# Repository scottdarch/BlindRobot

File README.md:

```
.            ``
      <X X>  /
 ``---  |  -
     [     ]   A BlindRobot Project (by 32bits.io)
 _____U___U____________________________________________________________________
```

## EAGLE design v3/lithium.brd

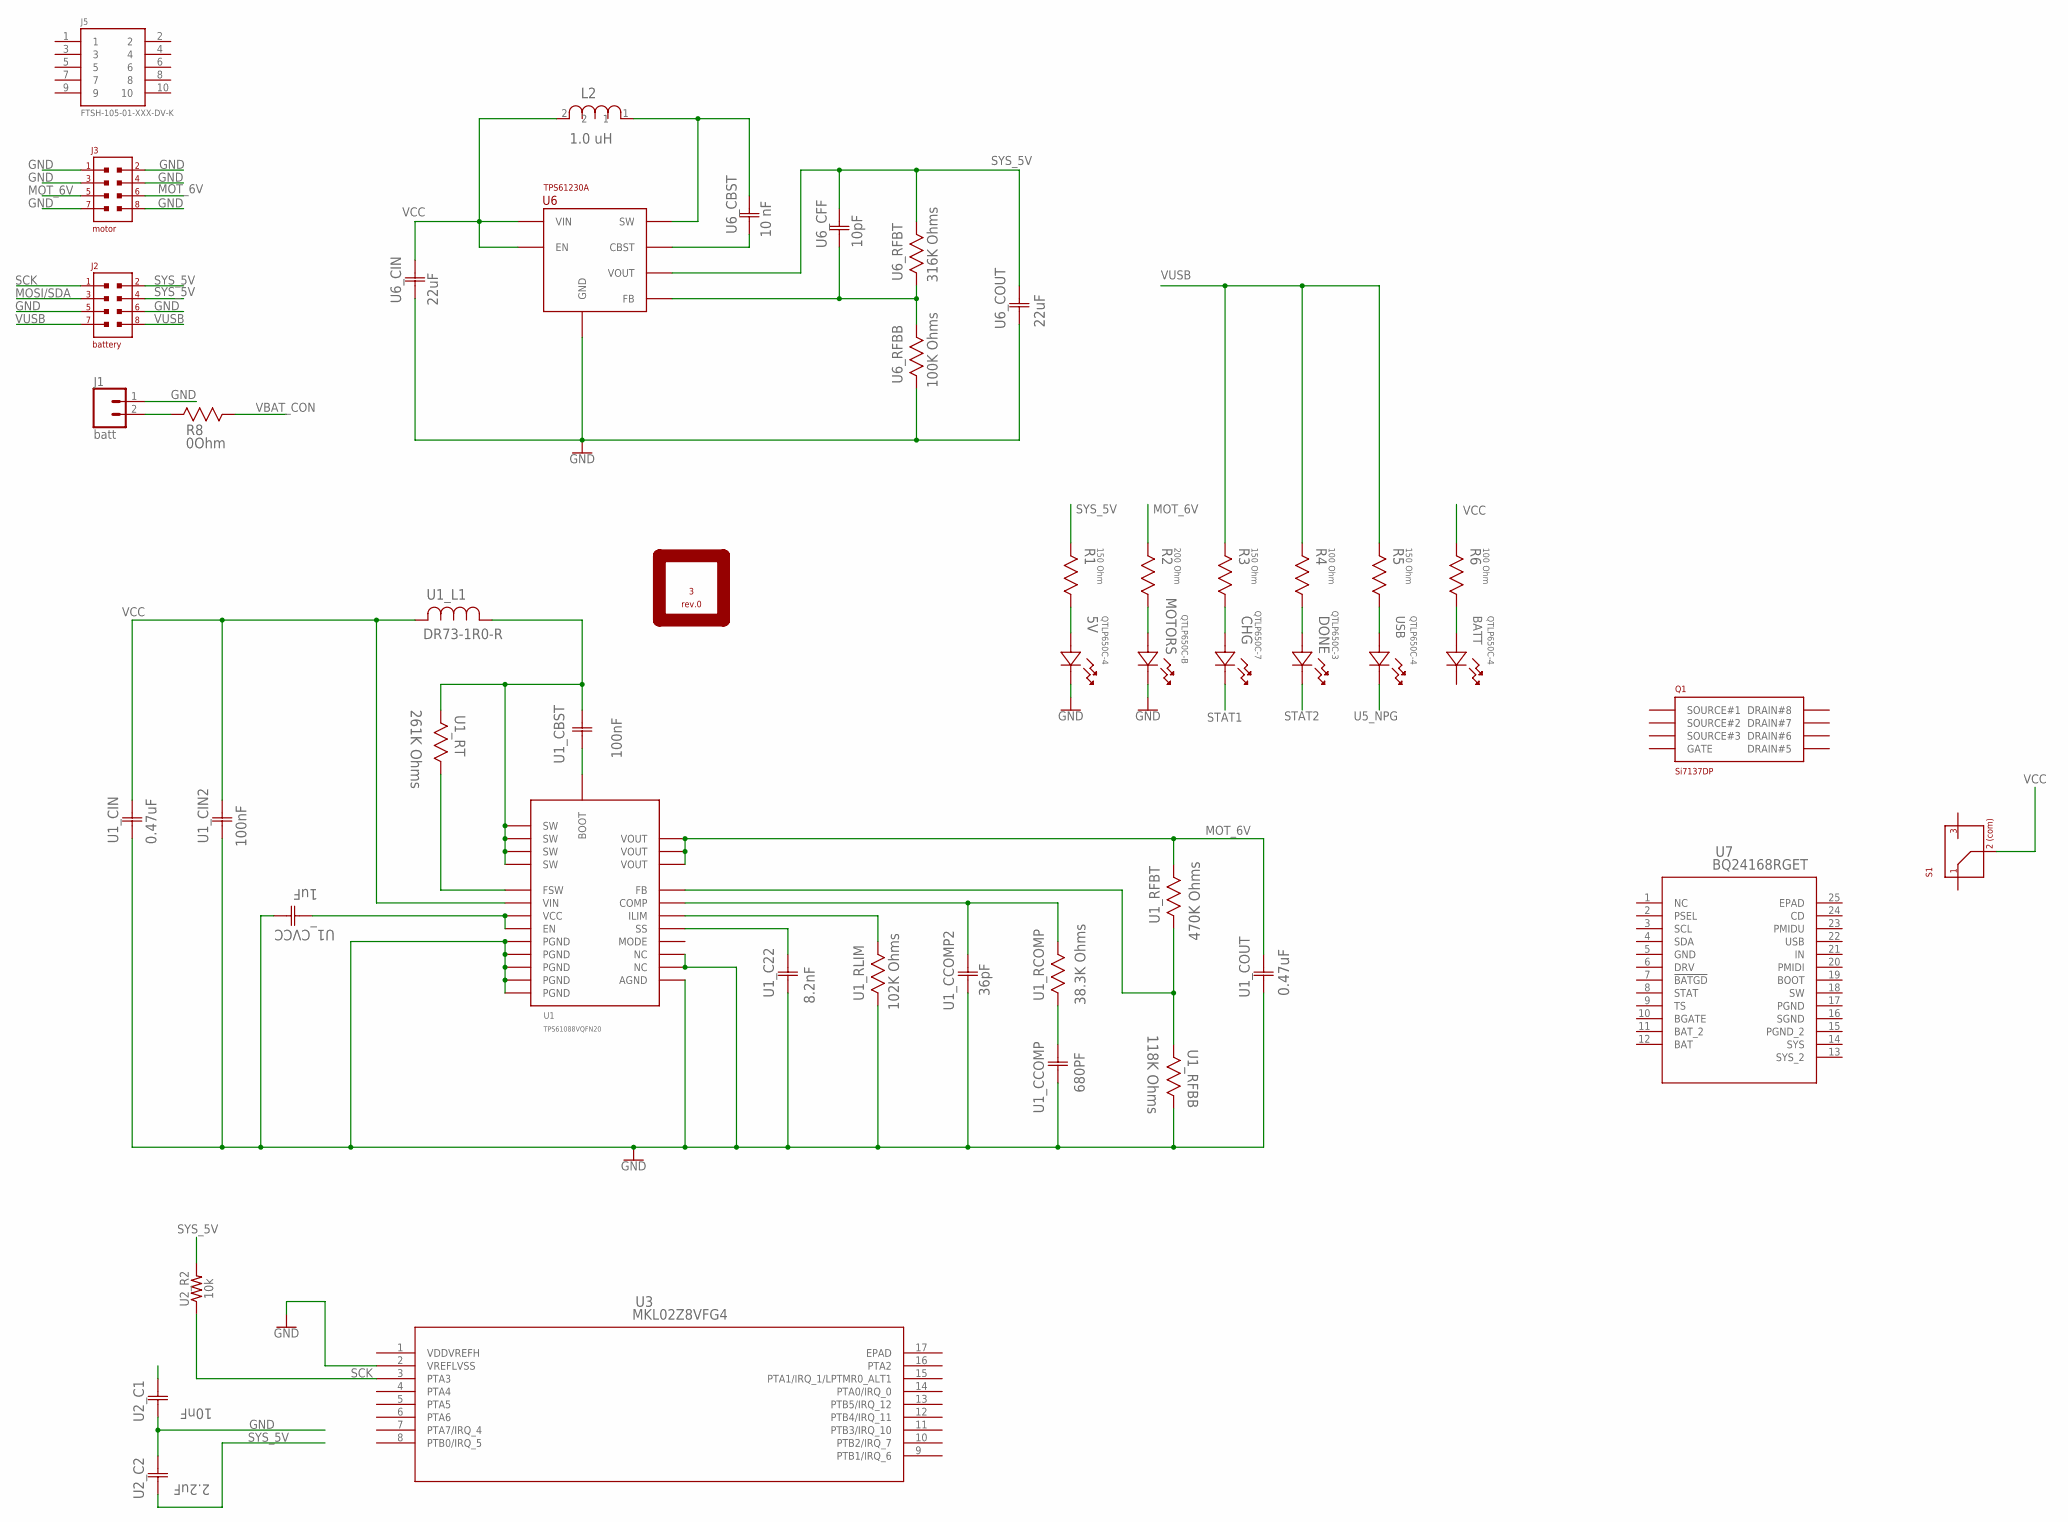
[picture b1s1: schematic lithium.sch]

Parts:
3: rev.0; PERIODIC_SYMBOL_BACK
5V: QTLP650C-4; LED_597-3311-407F
BATT: QTLP650C-4; LED_597-3311-407F
CHG: QTLP650C-7; LED_597-3111-407F
DONE: QTLP650C-3; LED_597-3401-407F
J1: batt; JST-2-SMD
J2: battery; 2X4-0.01"(2.54MM)-SOCKET
J3: motor; 2X4-0.01"(2.54MM)-SOCKET
J5: FTSH-105-01-XXX-DV-K
L2: 1.0 uH; INDC3225X22N
MOTORS: QTLP650C-B; LED_597-3311-402F
Q1: Si7137DP; SO-8
R1, R3, R5: 150 Ohm; RESC2013X65N
R2: 200 Ohm; RESC2013X65N
R4, R6: 100 Ohm; RESC2013X65N
R8: 0Ohm; RESC2013X65N
S1: SS312SAH4
U1: TPS61088VQFN20; VQFN20
U1_C22: 8.2nF; CAPC1005X60N
U1_CBST: 100nF; CAPC2013X94N
U1_CCOMP: 680PF; CAPC1608X90N
U1_CCOMP2: 36pF; CAPC1005X60N
U1_CIN, U1_COUT: 0.47uF; CAPC3216X180N
U1_CIN2: 100nF; CAPC1005X60N
U1_CVCC: 1uF; CAPC1608X85N
U1_L1: DR73-1R0-R; INDM7676X355N
U1_RCOMP: 38.3K Ohms; RESC1005X40N
U1_RFBB: 118K Ohms; RESC1005X40N
U1_RFBT: 470K Ohms; RESC1608X60N
U1_RLIM: 102K Ohms; RESC1005X40N
U1_RT: 261K Ohms; RESC1005X40N
U2_C1: 10nF; CAPC1005X55N
U2_C2: 2.2uF; CAPC1005X60N
U2_R2: 10k; 0402
U3: MKL02Z8VFG4; QFN-16_3X3X0.65
U6: TPS61230A; VQFN7
U6_CBST: 10 nF; CAPC1005X60N
U6_CFF: 10pF; CAPC1608X85N
U6_CIN: 22uF; CAPC2013X135N
U6_COUT: 22uF; CAPC3225X270N
U6_RFBB: 100K Ohms; RESC1005X40N
U6_RFBT: 316K Ohms; RESC1005X40N
U7: BQ24168RGET; RGE24_2P7X2P7
USB: QTLP650C-4; LED_597-3311-407F

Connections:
BOOT: U1.P$8 (BOOT), U1_CBST.1 (C1)
FB: U1.P$17 (FB), U1_RFBB.2, U1_RFBT.2 (R2)
FSW: U1.P$3 (FSW), U1_RT.1
GND: 5V.1, J1.1 (2), J2.P$5 (5), J2.P$6 (6), J3.P$1 (1), J3.P$2 (2), J3.P$3 (3), J3.P$4 (4), J3.P$7 (7), J3.P$8 (8), MOTORS.1, U1.P$11 (NC), U1.P$12 (NC), U1.P$20 (AGND), U1.P$21 (PGND), U1.P$22 (PGND), U1.P$23 (PGND), U1.P$24 (PGND), U1.P$25 (PGND), U1_C22.1 (C1), U1_CCOMP.1 (C1), U1_CCOMP2.1 (C1), U1_CIN.1 (C1), U1_CIN2.1 (C1), U1_COUT.1 (C1), U1_CVCC.2 (C2), U1_RFBB.1, U1_RLIM.2, U2_C1.1 (C1), U2_C2.1 (C2), U3.2 (VREFLVSS), U6.P$6 (GND), U6_CIN.1 (C1), U6_COUT.1 (C1), U6_RFBB.2, U7.5 (GND)
ILIM: U1.P$19 (ILIM), U1_RLIM.1
LA_5: 5V.2, R1.1 (R1)
LA_6: MOTORS.2, R2.1 (R1)
LA_BATT: BATT.2, R6.1 (R1)
LA_CHG: CHG.2, R3.1 (R1)
LA_DONE: DONE.2, R4.1 (R1)
LA_USB: R5.1 (R1), USB.2
MOSI/SDA: J2.P$3 (3)
MOT_6V: J3.P$5 (5), J3.P$6 (6), R2.2 (R2), U1.P$14 (VOUT), U1.P$15 (VOUT), U1.P$16 (VOUT), U1_COUT.2 (C2), U1_RFBT.1 (R1)
unnamed: U1_CCOMP.2 (C2), U1_RCOMP.2
PGND: U7.17 (PGND)
PGND_2: U7.15 (PGND_2)
SCK: J2.P$1 (1), U2_R2.1, U3.3 (PTA3)
SGND: U7.16 (SGND)
SS: U1.P$10 (SS), U1_C22.2 (C2)
STAT1: CHG.1
STAT2: DONE.1
SW: U1.P$4 (SW), U1.P$5 (SW), U1.P$6 (SW), U1.P$7 (SW), U1_CBST.2 (C2), U1_L1.1, U1_RT.2
SYS_5V: J2.P$2 (2), J2.P$4 (4), R1.2 (R2), U2_C1.2 (C2), U2_C2.2 (C1), U2_R2.2, U6.P$7 (VOUT), U6_CFF.2 (C2), U6_COUT.2 (C2), U6_RFBT.1
U1_COMP: U1.P$18 (COMP), U1_CCOMP2.2 (C2), U1_RCOMP.1
U1_VCC: U1.P$1 (VCC), U1.P$2 (EN), U1_CVCC.1 (C1)
U5_NPG: USB.1
U6_CBST: U6.P$1 (CBST), U6_CBST.1 (C1)
U6_FB: U6.P$3 (FB), U6_CFF.1 (C1), U6_RFBB.1, U6_RFBT.2
U6_SW: L2.1, U6.P$5 (SW), U6_CBST.2 (C2)
VBAT_CON: R8.1
VBAT_JST: J1.2 (1), R8.2
VCC: L2.2, R6.2 (R2), S1.P$2, U1.P$9 (VIN), U1_CIN.2 (C2), U1_CIN2.2 (C2), U1_L1.2, U6.P$2 (EN), U6.P$4 (VIN), U6_CIN.2 (C2)
VDDVREFH: U3.1 (VDDVREFH)
VUSB: J2.P$7 (7), J2.P$8 (8), R3.2 (R2), R4.2 (R2), R5.2 (R2)

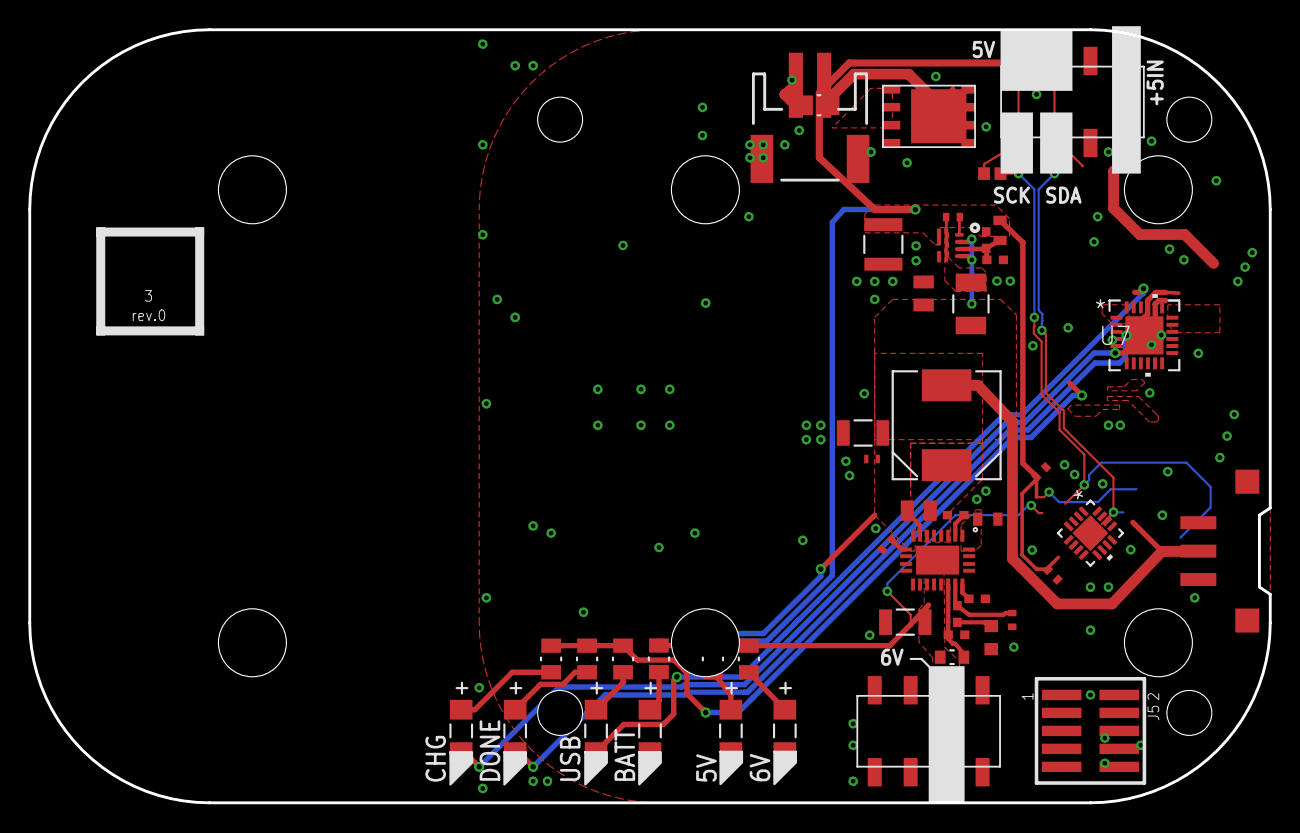
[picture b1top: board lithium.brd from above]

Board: 2 copper layers, 87.6 x 54.6 mm, 48 parts (1 on the bottom side), 25 nets.

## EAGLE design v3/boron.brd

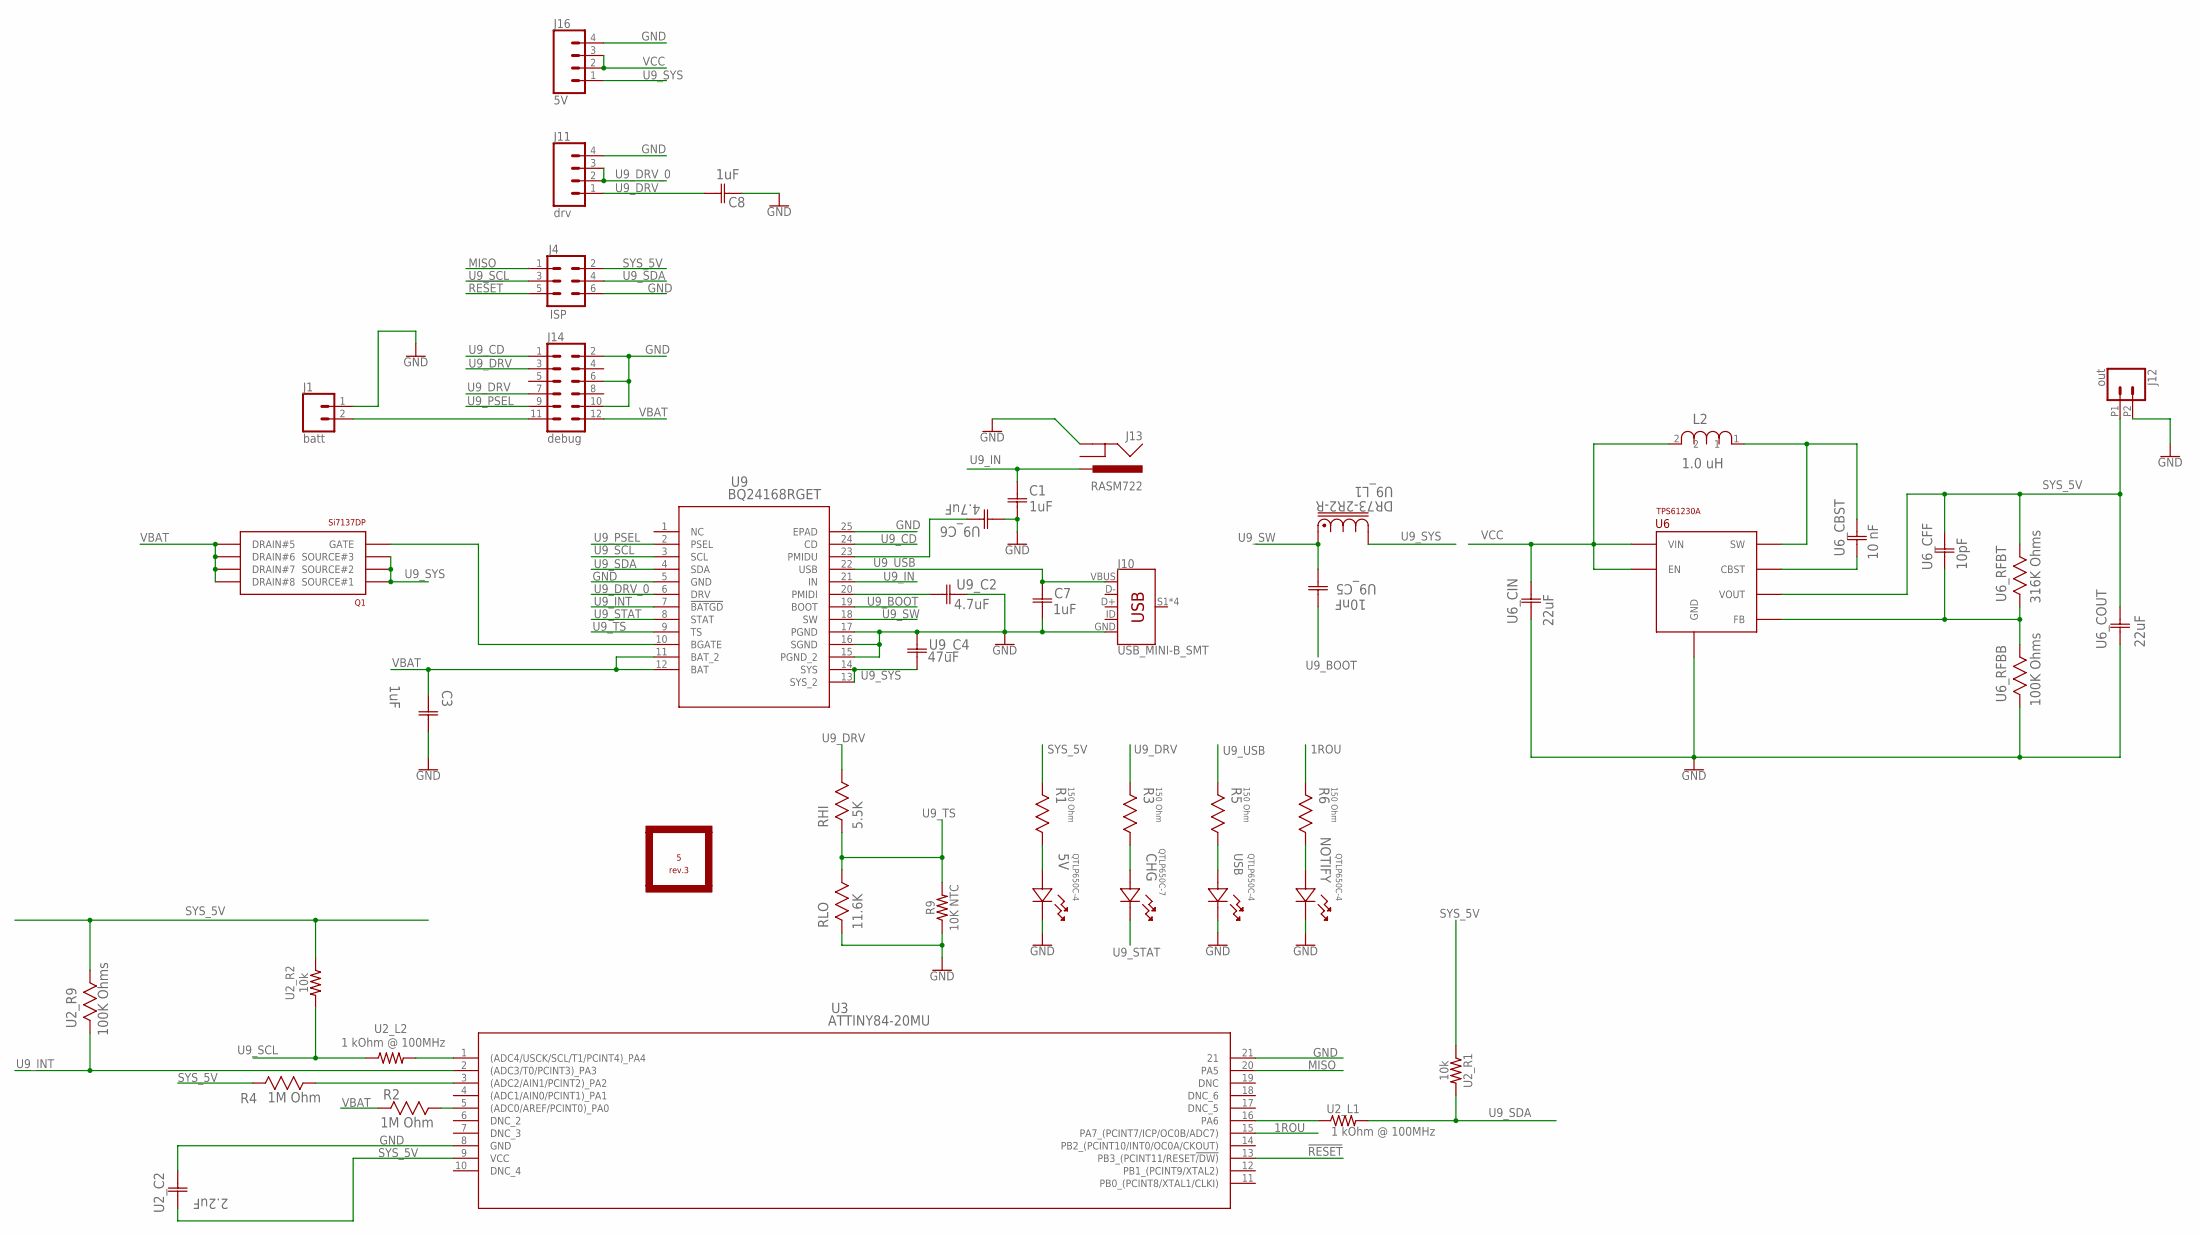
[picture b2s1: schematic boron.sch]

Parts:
5: rev.3; PERIODIC_SYMBOL_BACK
5V: QTLP650C-4; LED_597-3311-407F
C1, C3, C7, C8: 1uF; CAPC1608X94N
CHG: QTLP650C-7; LED_597-3111-407F
J1: batt; JST-2-SMD
J4: ISP; 2X3
J10: USB_MINI-B_SMT; USB-MINIB
J11: drv; 1X04
J12: out; 1X02_2.54_SCREWTERM
J13: RASM722
J14: debug; 2X6
J16: 5V; 1X04
L2: 1.0 uH; INDC3225X22N
NOTIFY: QTLP650C-4; LED_597-3311-407F
Q1: Si7137DP; SO-8
R1, R3, R5, R6: 150 Ohm; RESC2013X65N
R2, R4: 1M Ohm; RESC1608X60N
R9: 10K NTC; 1206
RHI: 5.5K; RESC1608X60N
RLO: 11.6K; RESC1608X60N
U2_C2: 2.2uF; CAPC1005X60N
U2_L1, U2_L2: 1 kOhm @ 100MHz; 0402
U2_R1, U2_R2: 10k; 0402
U2_R9, U6_RFBB: 100K Ohms; RESC1005X40N
U3: ATTINY84-20MU; 20M1
U6: TPS61230A; VQFN7
U6_CBST: 10 nF; CAPC1005X60N
U6_CFF: 10pF; CAPC1608X85N
U6_CIN: 22uF; CAPC2013X135N
U6_COUT: 22uF; CAPC3225X270N
U6_RFBT: 316K Ohms; RESC1005X40N
U9: BQ24168RGET; RGE24_2P7X2P7
U9_C2, U9_C6: 4.7uF; CAPC2013X140N
U9_C4: 47uF; CAPC3216X127N
U9_C5: 10nF; CAPC1608X90N
U9_L1: DR73-2R2-R; DR73
USB: QTLP650C-4; LED_597-3311-407F

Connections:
1ROU: R6.2 (R2), U3.15 (PA7_(PCINT7/ICP/OC0B/ADC7))
!RESET: J4.5, U3.13 (PB3_(PCINT11/RESET!/DW))
ADC0: R2.1, U3.5 ((ADC0/AREF/PCINT0)_PA0)
ADC2: R4.1, U3.3 ((ADC2/AIN1/PCINT2)_PA2)
GND: 5V.1, C1.2 (C2), C3.2 (C2), C7.2 (C2), C8.1 (C1), J1.1 (2), J4.6, J10.GND, J11.4, J12.P2 (2), J13.SLEEVE (GND), J14.2, J14.6, J14.10, J16.4, NOTIFY.1, R9.1, RLO.2, U2_C2.1 (C2), U3.8 (GND), U3.21, U6.P$6 (GND), U6_CIN.1 (C1), U6_COUT.1 (C1), U6_RFBB.2, U9.5 (GND), U9.15 (PGND_2), U9.16 (SGND), U9.17 (PGND), U9.25 (EPAD), U9_C2.2 (C2), U9_C4.1 (C1), U9_C6.2 (C2), USB.1
GNDBREAK: J13.SHUNT (GNDBREAK)
LA_1: NOTIFY.2, R6.1 (R1)
LA_5: 5V.2, R1.1 (R1)
LA_CHG: CHG.2, R3.1 (R1)
LA_USB: R5.1 (R1), USB.2
MISO: J4.1, U3.20 (PA5)
SYS_5V: J4.2, J12.P1 (1), R1.2 (R2), R4.2, U2_C2.2 (C1), U2_R1.1, U2_R2.1, U2_R9.1, U3.9 (VCC), U6.P$7 (VOUT), U6_CFF.2 (C2), U6_COUT.2 (C2), U6_RFBT.1
U3_PA4: U2_L2.2, U3.1 ((ADC4/USCK/SCL/T1/PCINT4)_PA4)
U3_PA6: U2_L1.1, U3.16 (PA6)
U6_CBST: U6.P$1 (CBST), U6_CBST.1 (C1)
U6_FB: U6.P$3 (FB), U6_CFF.1 (C1), U6_RFBB.1, U6_RFBT.2
U6_SW: L2.1, U6.P$5 (SW), U6_CBST.2 (C2)
U9_BGATE: Q1.P$4 (GATE), U9.10 (BGATE)
U9_BOOT: U9.19 (BOOT), U9_C5.1 (C1)
U9_CD: J14.1, U9.24 (CD)
U9_DRV: C8.2 (C2), J11.1, J14.3, J14.7, R3.2 (R2), RHI.1
U9_DRV_0: J11.2, J11.3, U9.6 (DRV)
U9_IN: C1.1 (C1), J13.TIP (PWR), U9.21 (IN)
U9_INT: U2_R9.2, U3.2 ((ADC3/T0/PCINT3)_PA3), U9.7 (!BATGD)
U9_PMIDI: U9.20 (PMIDI), U9_C2.1 (C1)
U9_PMIDU: U9.23 (PMIDU), U9_C6.1 (C1)
U9_PSEL: J14.9, U9.2 (PSEL)
U9_SCL: J4.3, U2_L2.1, U2_R2.2, U9.3 (SCL)
U9_SDA: J4.4, U2_L1.2, U2_R1.2, U9.4 (SDA)
U9_STAT: CHG.1, U9.8 (STAT)
U9_SW: U9.18 (SW), U9_C5.2 (C2), U9_L1.1
U9_SYS: J16.1, Q1.P$1 (SOURCE#1), Q1.P$2 (SOURCE#2), Q1.P$3 (SOURCE#3), U9.13 (SYS_2), U9.14 (SYS), U9_C4.2 (C2), U9_L1.2
U9_TS: R9.2, RHI.2, RLO.1, U9.9 (TS)
U9_USB: C7.1 (C1), J10.VBUS, R5.2 (R2), U9.22 (USB)
VBAT: C3.1 (C1), J14.12, Q1.P$5 (DRAIN#5), Q1.P$6 (DRAIN#6), Q1.P$7 (DRAIN#7), Q1.P$8 (DRAIN#8), Q1.P$9 (DRAIN#8), R2.2, U9.11 (BAT_2), U9.12 (BAT)
VBAT_CON: J1.2 (1), J14.11
VCC: J16.2, J16.3, L2.2, U6.P$2 (EN), U6.P$4 (VIN), U6_CIN.2 (C2)

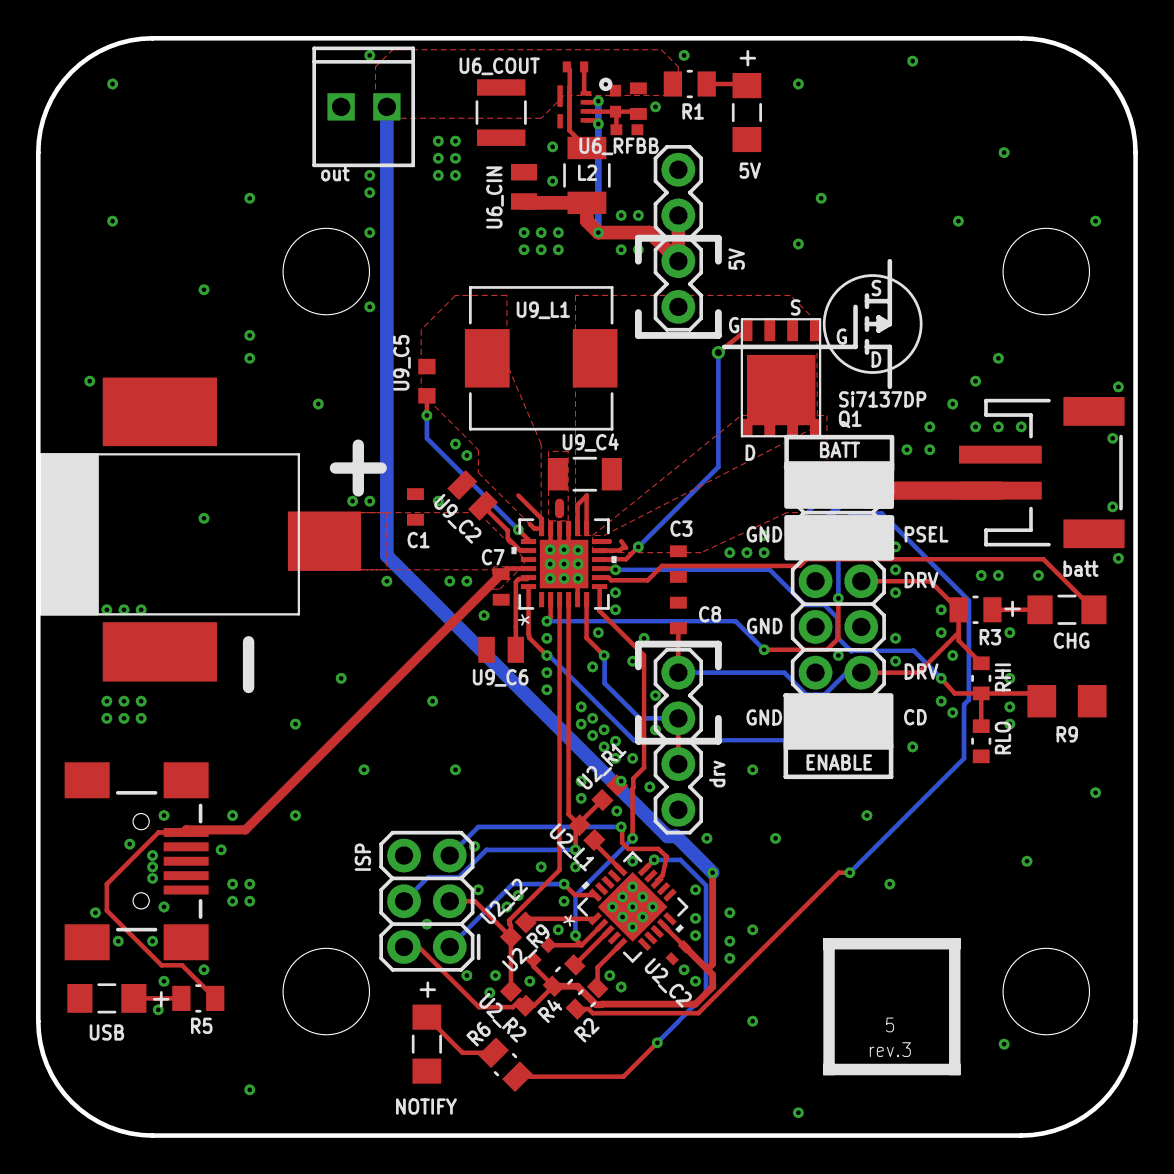
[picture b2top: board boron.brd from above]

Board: 2 copper layers, 61.0 x 61.0 mm, 48 parts (1 on the bottom side), 36 nets.

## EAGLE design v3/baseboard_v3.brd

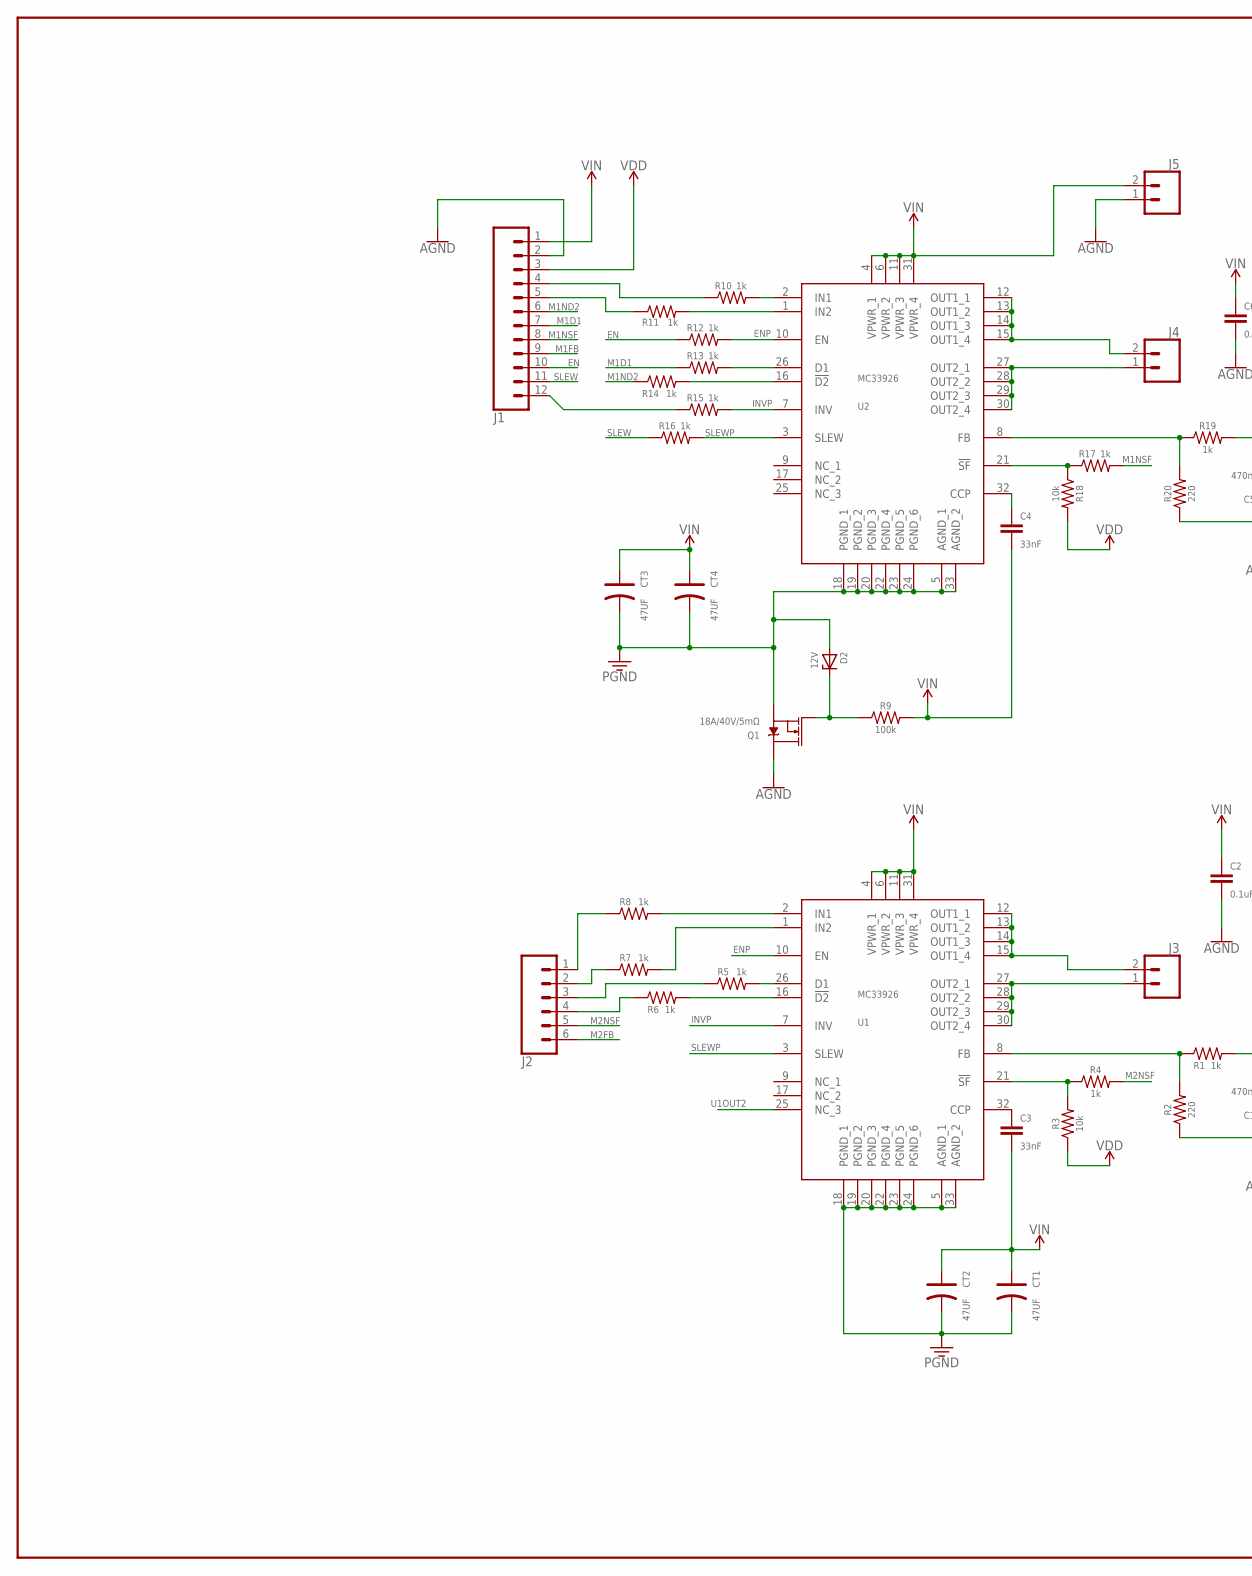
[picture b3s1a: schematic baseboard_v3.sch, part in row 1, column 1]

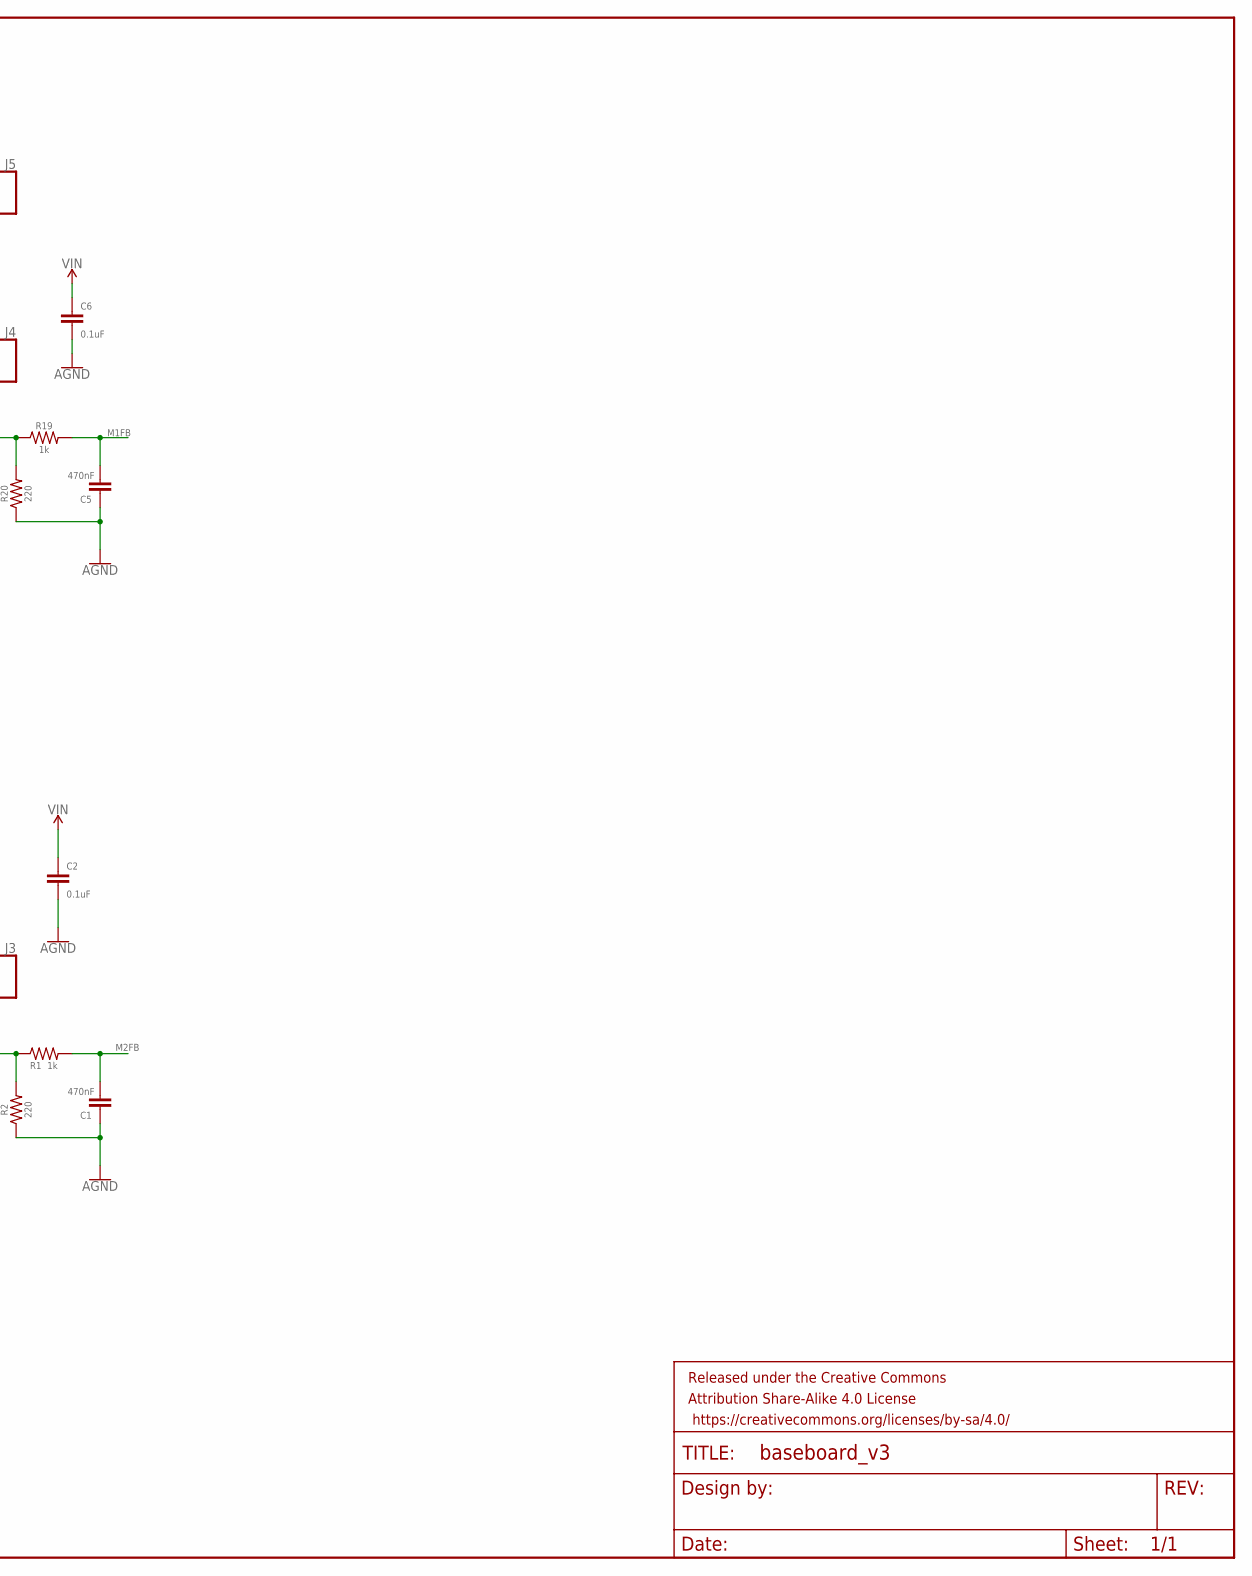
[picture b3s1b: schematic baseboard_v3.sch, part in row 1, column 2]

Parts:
C1, C5: 470nF; 0402
C2, C6: 0.1uF; 0603
C3, C4: 33nF; 0603
CT1, CT2, CT3, CT4: 47UF; ELECTRO-SMD-C-6MM
D2: 12V; SOD80C
FRAME1: FRAME-LEDGER; CREATIVE_COMMONS
J1: CONN_12NO_SILK; 1X12_NO_SILK
J2: CONN_06NO_SILK_FEMALE_PTH; 1X06_NO_SILK
J3, J4, J5: CONN_023.5MM-NO_SILK; SCREWTERMINAL-3.5MM-2-NS
Q1: 18A/40V/5mΩ; SO08
R1, R4, R5, R6, R7, R8, R10, R11, R12, R13, R14, R15, R16, R17, R19: 1k; 0603
R2, R20: 220; 0603
R3, R18: 10k; 0603
R9: 100k; 0603
U1, U2: MC33926; PQFN32_0P8_8X8_SLUG

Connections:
AGND: C1.1, C2.2, C5.1, C6.2, J1.2, J5.1, Q1.5 (D), Q1.6 (D), Q1.7 (D), Q1.8 (D), R2.1, R20.1
EN: J1.10, R12.1
ENP: R12.2, U1.10 (EN), U2.10 (EN)
INV: J1.12, R15.1
INVP: R15.2, U1.7 (INV), U2.7 (INV)
M1D1: J1.7, R13.1
M1FB: C5.2, J1.9, R19.2
M1IN1: J1.4, R10.1
M1IN2: J1.5, R11.1
M1ND2: J1.6, R14.1
M1NSF: J1.8, R17.2
M2D1: J2.3, R5.1
M2FB: C1.2, J2.6, R1.2
M2IN1: J2.1 (>NAME), R8.1
M2IN2: J2.2, R7.1
M2ND2: J2.4, R6.1
M2NSF: J2.5, R4.2
PGND: CT1.-, CT2.-, CT3.-, CT4.-, D2.A, Q1.1 (S), Q1.2 (S), Q1.3 (S), U1.5 (AGND_1), U1.18 (PGND_1), U1.19 (PGND_2), U1.20 (PGND_3), U1.22 (PGND_4), U1.23 (PGND_5), U1.24 (PGND_6), U1.33 (AGND_2), U2.5 (AGND_1), U2.18 (PGND_1), U2.19 (PGND_2), U2.20 (PGND_3), U2.22 (PGND_4), U2.23 (PGND_5), U2.24 (PGND_6), U2.33 (AGND_2)
SLEW: J1.11, R16.1
SLEWP: R16.2, U1.3 (SLEW), U2.3 (SLEW)
U1CCP: C3.1, U1.32 (CCP)
U1D1: R5.2, U1.26 (D1)
U1FB: R1.1, R2.2, U1.8 (FB)
U1IN1: R8.2, U1.2 (IN1)
U1IN2: R7.2, U1.1 (IN2)
U1ND2: R6.2, U1.16 (!D2)
U1NSF: R3.2, R4.1, U1.21 (!SF)
U1OUT1: J3.2, U1.12 (OUT1_1), U1.13 (OUT1_2), U1.14 (OUT1_3), U1.15 (OUT1_4)
U1OUT2: J3.1, U1.25 (NC_3), U1.27 (OUT2_1), U1.28 (OUT2_2), U1.29 (OUT2_3), U1.30 (OUT2_4)
U2CCP: C4.1, U2.32 (CCP)
U2D1: R13.2, U2.26 (D1)
U2FB: R19.1, R20.2, U2.8 (FB)
U2IN1: R10.2, U2.2 (IN1)
U2IN2: R11.2, U2.1 (IN2)
U2ND2: R14.2, U2.16 (!D2)
U2NSF: R17.1, R18.1, U2.21 (!SF)
U2OUT1: J4.2, U2.12 (OUT1_1), U2.13 (OUT1_2), U2.14 (OUT1_3), U2.15 (OUT1_4)
U2OUT2: J4.1, U2.27 (OUT2_1), U2.28 (OUT2_2), U2.29 (OUT2_3), U2.30 (OUT2_4)
VCC: J1.3, R3.1, R18.2
VGATE: D2.C, Q1.4 (G), R9.1
VIN: C2.1, C3.2, C4.2, C6.1, CT1.+, CT2.+, CT3.+, CT4.+, J1.1, J5.2, R9.2, U1.4 (VPWR_1), U1.6 (VPWR_2), U1.11 (VPWR_3), U1.31 (VPWR_4), U2.4 (VPWR_1), U2.6 (VPWR_2), U2.11 (VPWR_3), U2.31 (VPWR_4)

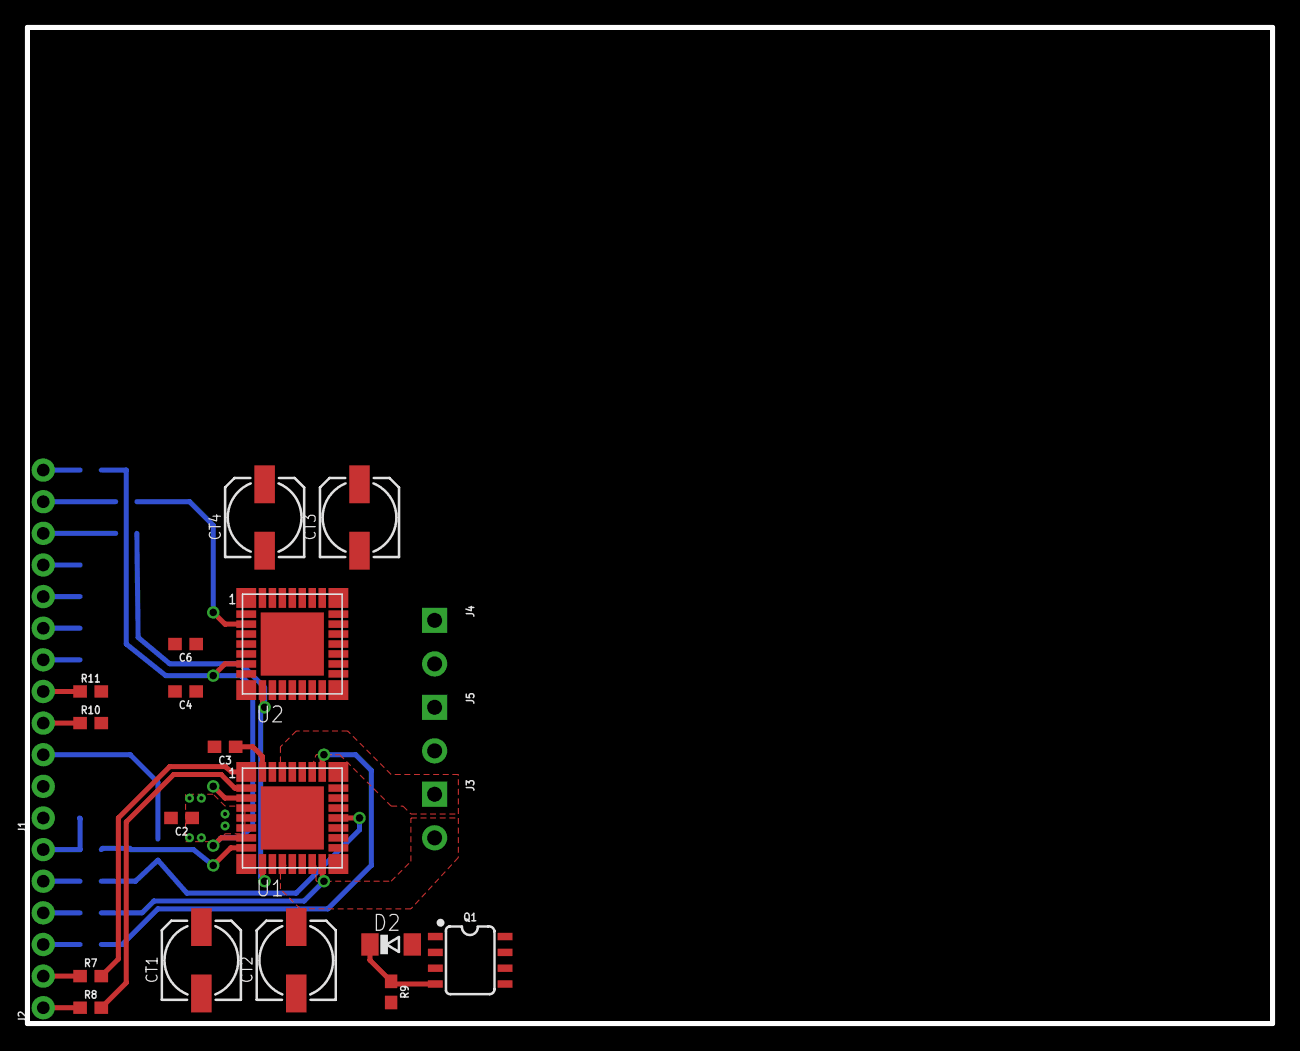
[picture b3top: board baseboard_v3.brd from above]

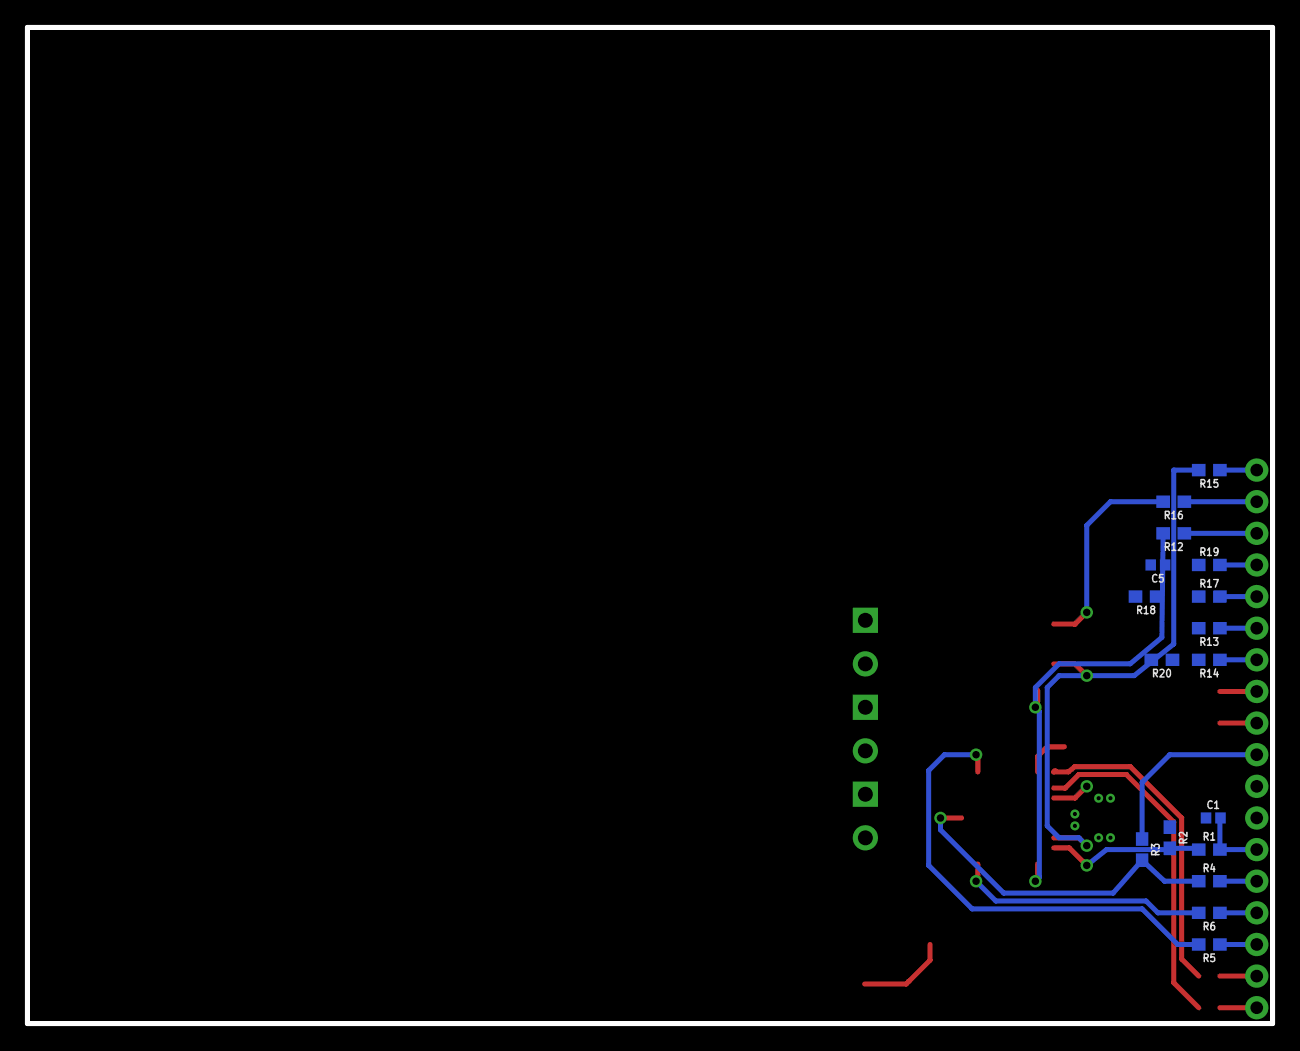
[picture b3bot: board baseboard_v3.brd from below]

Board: 2 copper layers, 100.0 x 80.0 mm, 40 parts (17 on the bottom side), 41 nets.

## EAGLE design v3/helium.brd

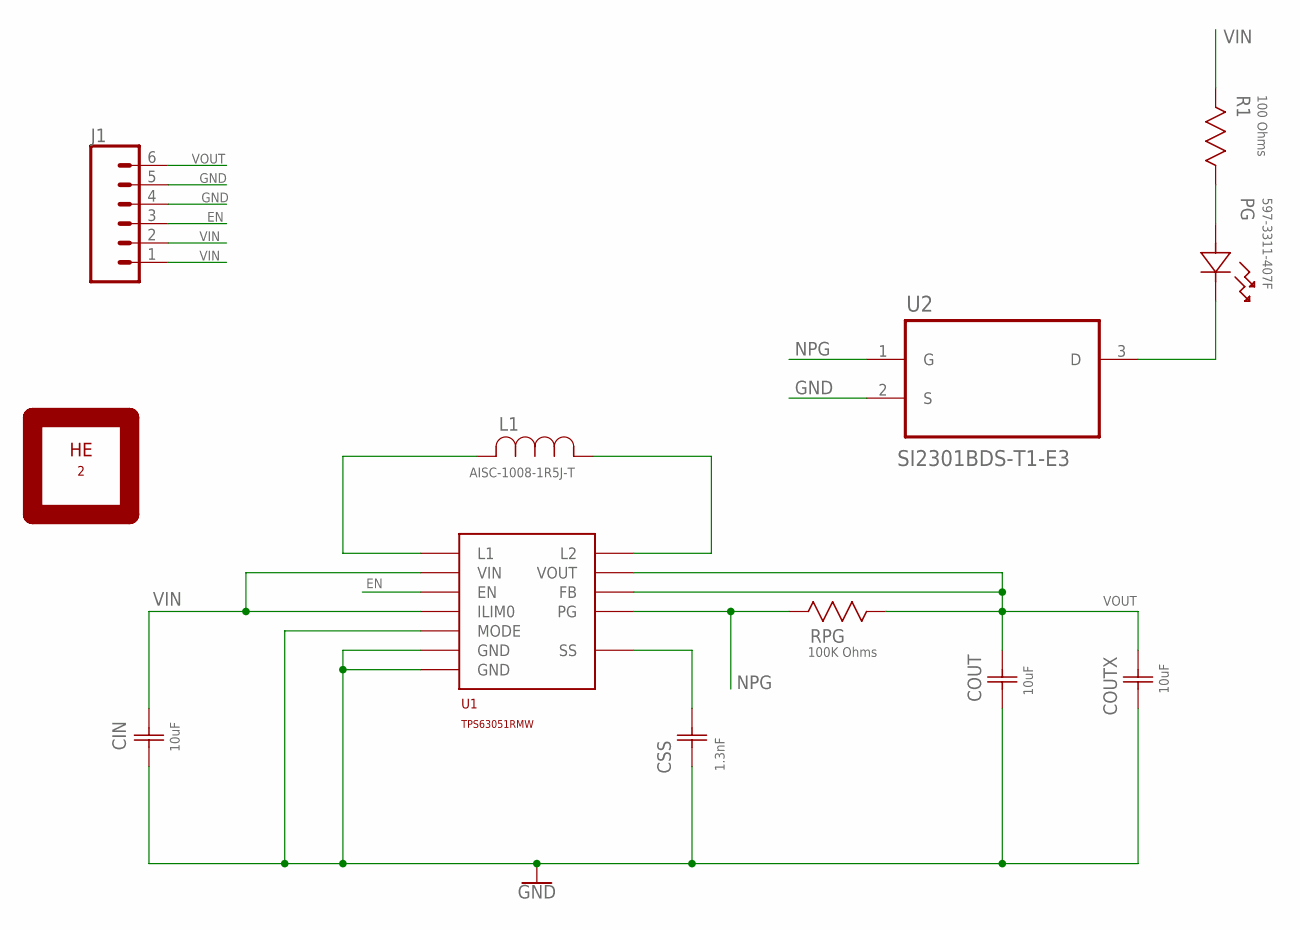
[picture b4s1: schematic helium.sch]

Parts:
CIN: 10uF; CAPC1608X85N
COUT: 10uF; CAPC1608X85N
COUTX: 10uF; CAPC1608X85N
CSS: 1.3nF; CAPC1005X60N
HE: 2; PERIODIC_SYMBOL_BACK
J1: CONN_06LONGPADS; 1X06_LONGPADS
L1: AISC-1008-1R5J-T; AISC-1008
PG: 597-3311-407F; LED_597-3311-407F
R1: 100 Ohms; RESC1005X40N
RPG: 100K Ohms; RESC1608X60N
U1: TPS63051RMW; RMW12
U2: SI2301BDS-T1-E3; SOT95P237X112-3N

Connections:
EN: J1.3, U1.P$11 (EN)
GND: CIN.1 (C1), COUT.1 (C1), COUTX.1 (C1), CSS.1 (C1), J1.4, J1.5, U1.P$2 (GND), U1.P$6 (MODE), U1.P$9 (GND), U2.2 (S)
L1: L1.2, U1.P$1 (L1)
L2: L1.1, U1.P$3 (L2)
unnamed: PG.1, U2.3 (D)
unnamed: PG.2, R1.1 (R1)
NPG: RPG.2, U1.P$8 (PG), U2.1 (G)
SS: CSS.2 (C2), U1.P$7 (SS)
VIN: CIN.2 (C2), J1.1 (>NAME), J1.2, R1.2 (R2), U1.P$10 (ILIM0), U1.P$12 (VIN)
VOUT: COUT.2 (C2), COUTX.2 (C2), J1.6, RPG.1, U1.P$4 (VOUT), U1.P$5 (FB)

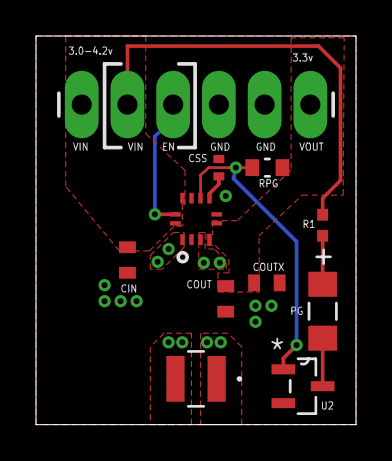
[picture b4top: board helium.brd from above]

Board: 2 copper layers, 17.8 x 21.6 mm, 12 parts (0 on the bottom side), 10 nets.

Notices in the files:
parts and their libraries:
SparkFun-Aesthetics: Licensing: Creative Commons ShareAlike 4.0 International - https://creativecommons.org/licenses/by-sa/4.0
SparkFun-Aesthetics: Released under the Creative Commons Attribution Share-Alike 4.0 License
SparkFun-Aesthetics: https://creativecommons.org/licenses/by-sa/4.0
